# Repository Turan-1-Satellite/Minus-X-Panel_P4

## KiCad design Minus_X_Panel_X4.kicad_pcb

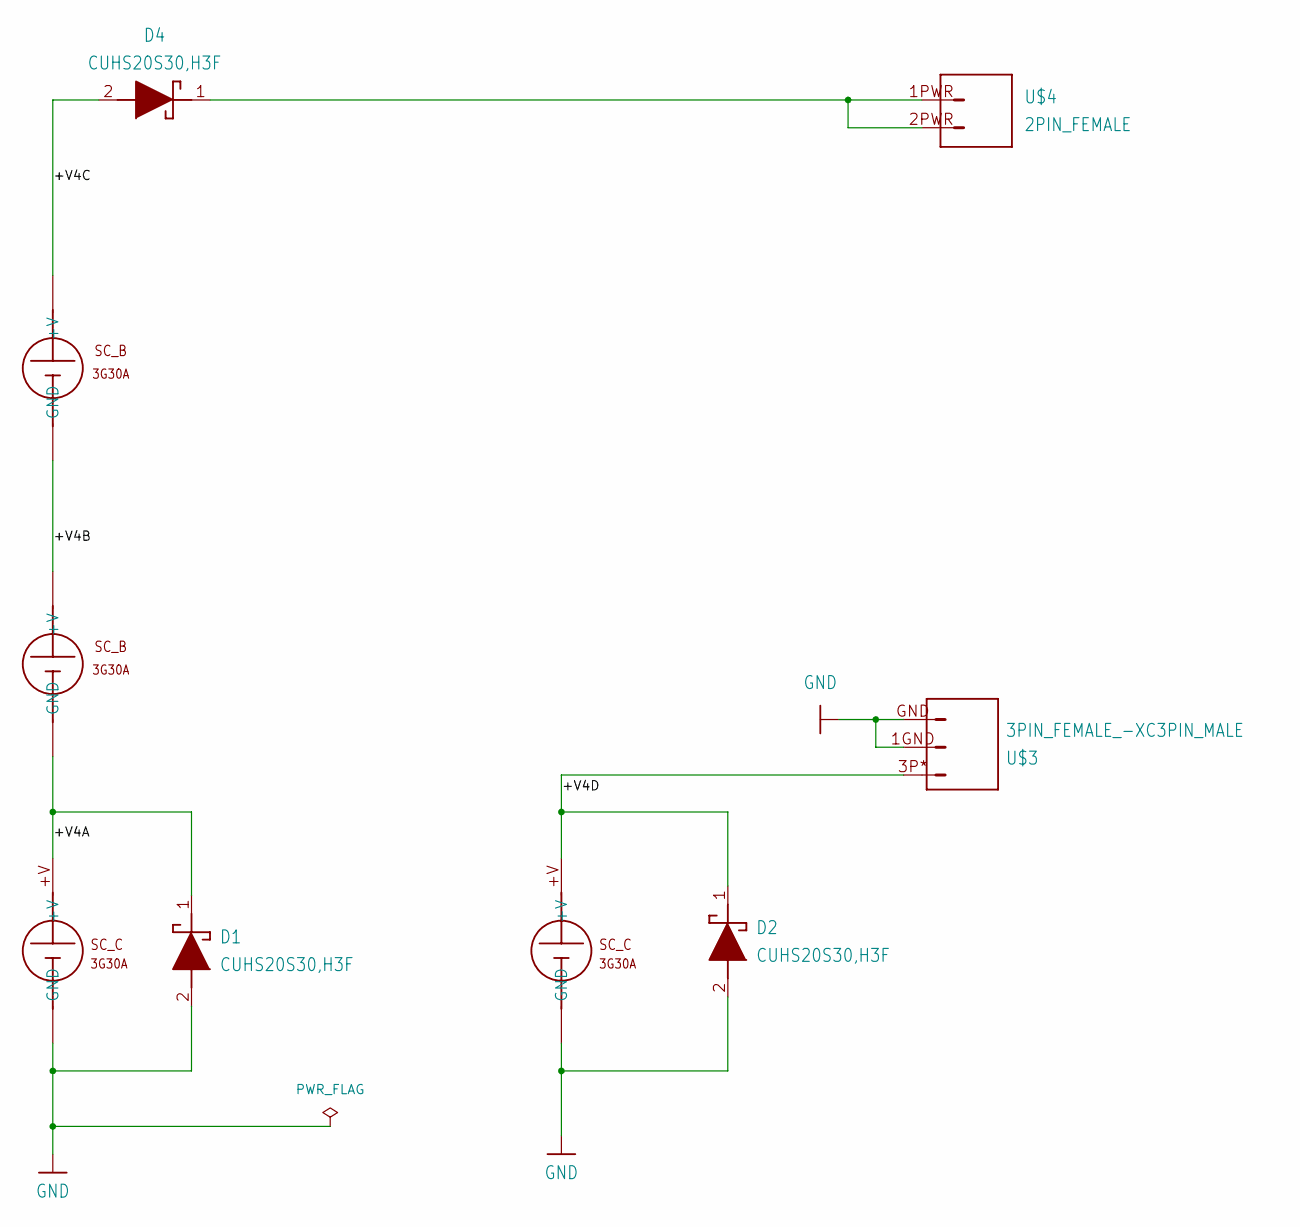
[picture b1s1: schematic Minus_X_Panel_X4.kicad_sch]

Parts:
D1, D2, D4: CUHS20S30,H3F
S1, S4: solar_cell_B
S2, S3: Solar_cell_C; solar_cell_C
U$3: 3PIN_FEMALE_-XC3PIN_MALE; FSR-41057-03-F
U$4: 2PIN_FEMALE; FSR-41057-02-F

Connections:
/+V4A: D1.1 (K), S2.+V, S4.GND
/+V4B: S1.GND, S4.+V
/+V4C: D4.2 (A), S1.+V
/+V4D: D2.1 (K), S3.+V, U$3.3P*
GND: D1.2 (A), D2.2 (A), S2.GND, S3.GND, U$3.1GND, U$3.GND
unnamed: D4.1 (K), U$4.1PWR, U$4.2PWR

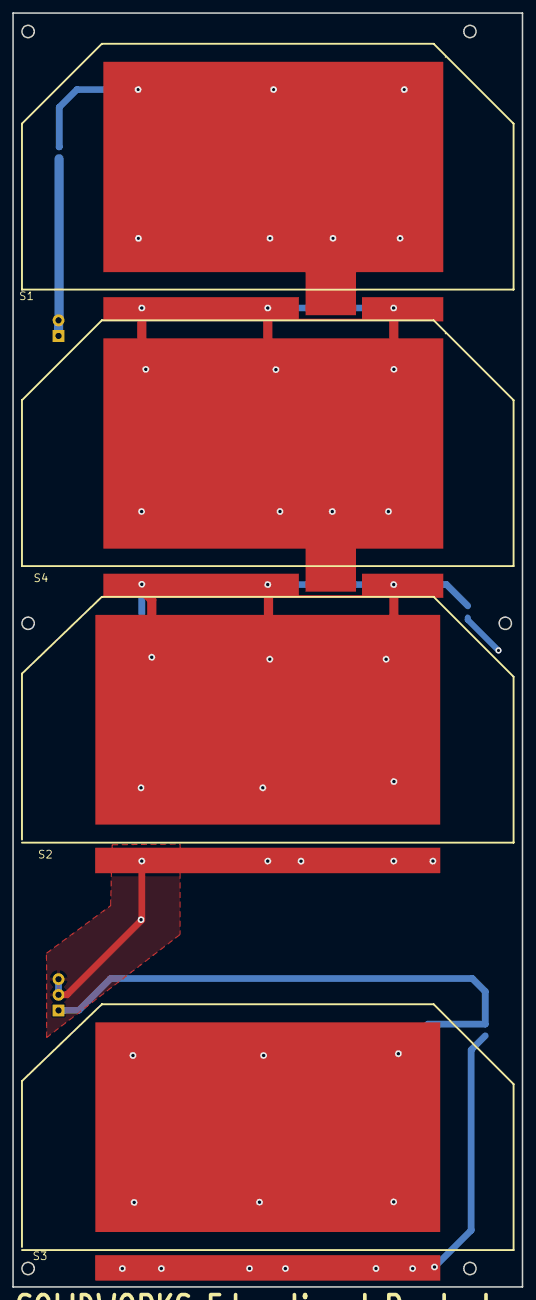
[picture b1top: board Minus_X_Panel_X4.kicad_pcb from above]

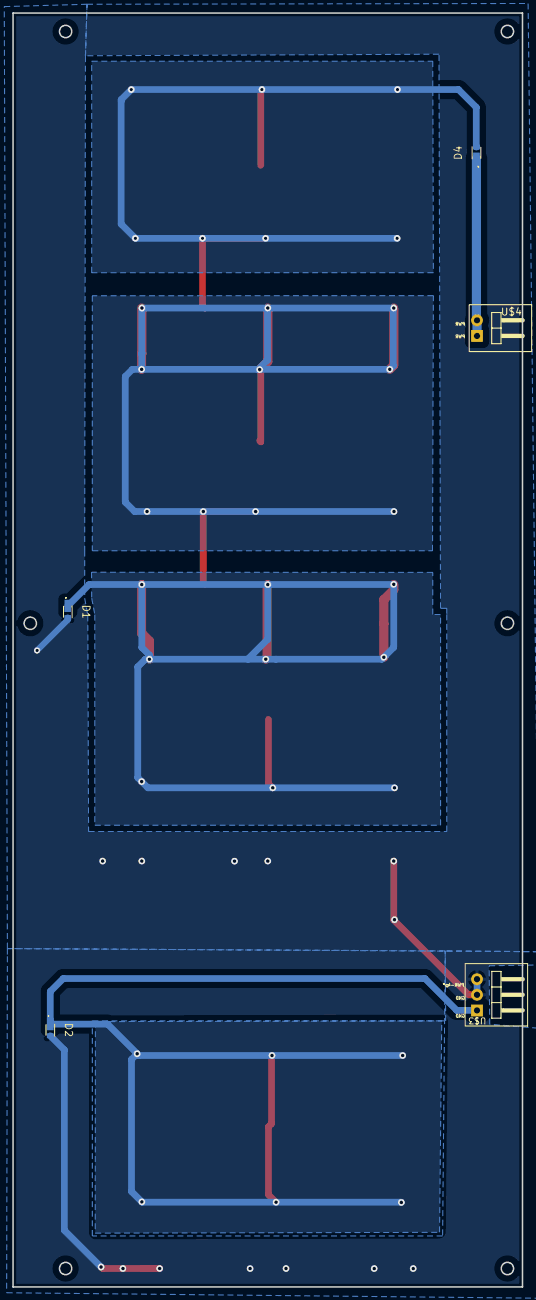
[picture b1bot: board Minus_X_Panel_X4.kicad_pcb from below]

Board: 2 copper layers, 82.9 x 207.3 mm, 9 parts (5 on the bottom side), 6 nets.

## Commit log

2026-03-18 Init
2026-03-18 Symbol, Footprint and 3D added for GPS connector
2026-03-18 Symbol, Footprint and 3D added for FSR-41057-02-F
2026-03-18 Prepare to push to Minus-X-part-4 repo
2026-03-18 Symbol and foot print id almost ready
2026-03-23 i updateed the PCB configuration of the panel
2026-03-24 -X Panel last updated the tracks
2026-03-25 footprint of the Panel is modified with tracking
2026-04-13 Updated the Pin Configuration
